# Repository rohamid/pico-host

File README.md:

# PICO HOST #
RP2040 board inspired by [Adafruit's RP2040 Feather Host](https://learn.adafruit.com/adafruit-feather-rp2040-with-usb-type-a-host). Board features:
* JST XH Li-ion/Li-po battery connector.
* Battery charger circuit.
* USB A Female connector for [PIO based USB](https://github.com/sekigon-gonnoc/Pico-PIO-USB).
* Adafruit's `STEMMA QT` I2C connector.

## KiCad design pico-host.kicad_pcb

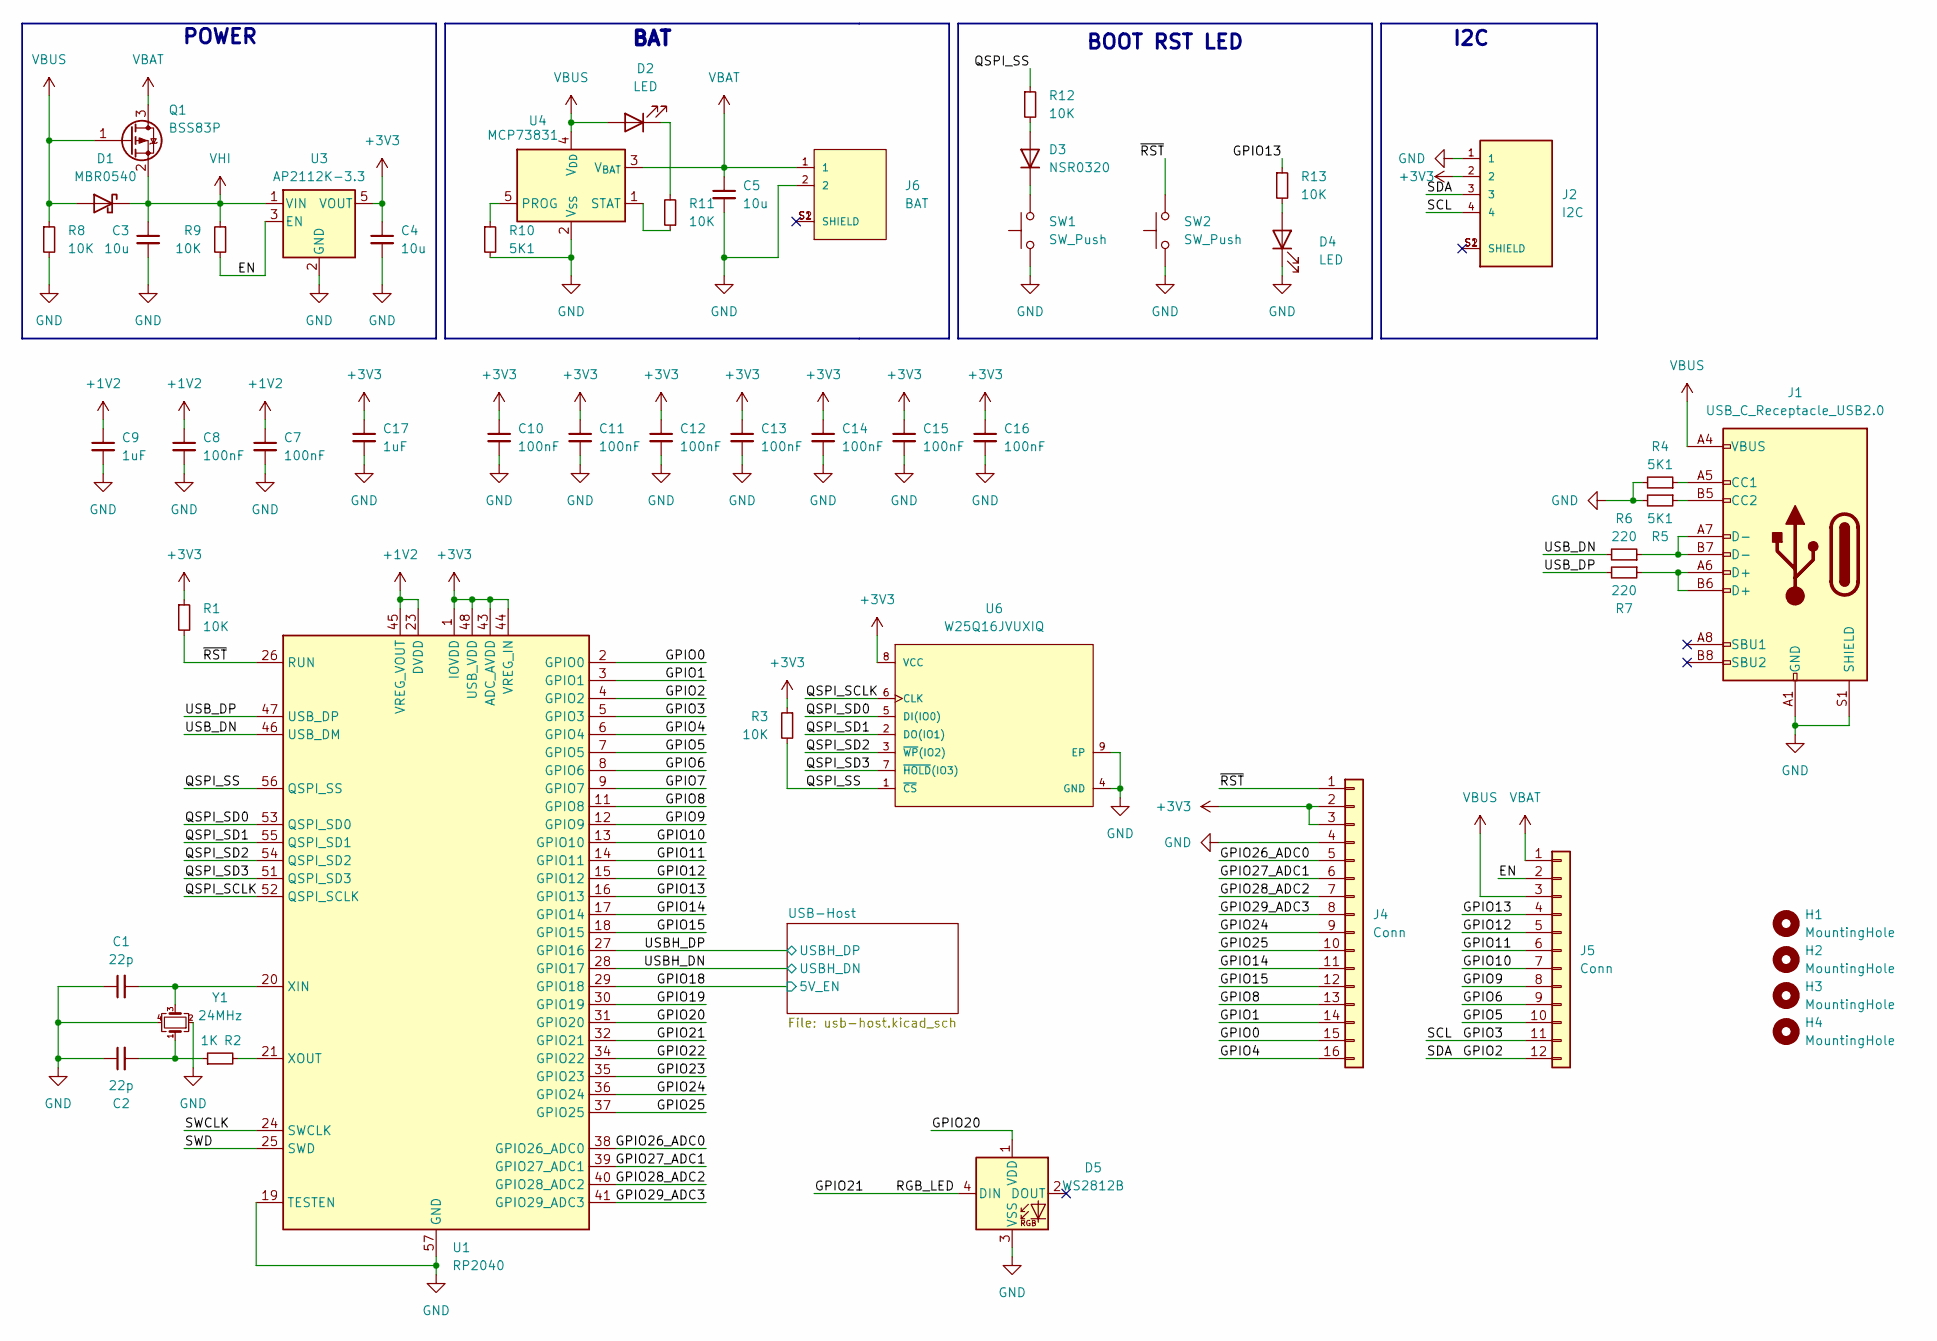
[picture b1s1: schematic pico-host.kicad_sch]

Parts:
C1, C2: 22p; C_0402_1005Metric
C3, C4, C5: 10u; C_0603_1608Metric
C7, C8, C10, C11, C12, C13, C14, C15, C16: 100nF; C_0402_1005Metric
C9: 1uF; C_0402_1005Metric
C17: 1uF; C_0603_1608Metric
D1: MBR0540; D_SOD-323
D2, D4: LED; LED_0603_1608Metric
D3: NSR0320; D_SOD-323
D5: WS2812B; LED_WS2812B-2020_PLCC4_2.0x2.0mm
H1, H2, H3, H4: MountingHole; MountingHole_2.5mm
J1: USB_C_Receptacle_USB2.0; USB_C_Receptacle_G-Switch_GT-USB-7010ASV
J2: I2C; JST_BM04B-SRSS-TB_LF__SN_
J4: Conn; PinHeader_1x16_P2.54mm_Vertical
J5: Conn; PinHeader_1x12_P2.54mm_Vertical
J6: BAT; JST_S2B-PH-SM4-TB_LF__SN_
Q1: BSS83P; TRANS_DMG3415UFY4Q-7
R1, R3, R8, R9, R11, R12, R13: 10K; R_0402_1005Metric
R2: 1K; R_0402_1005Metric
R4, R5, R10: 5K1; R_0402_1005Metric
R6, R7: 220; R_0402_1005Metric
SW1, SW2: SW_Push; SW_SPST_PTS810
U1: RP2040; QFN-56-1EP_7x7mm_P0.4mm_EP3.2x3.2mm
U3: AP2112K-3.3; SOT-23-5
U4: MCP73831; SOT-23-5
U6: W25Q16JVUXIQ; Winbond-UX-0-0-IPC_B; mouser part number 454-W25Q16JVUXIQTR; digikey description IC FLASH 16MBIT SPI/QUAD 8USON
Y1: 24MHz; Crystal_SMD_2520-4Pin_2.5x2.0mm

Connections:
+1V2: C7.1, C8.1, C9.1, U1.23 (DVDD), U1.45 (VREG_VOUT), U1.50 (DVDD)
+3V3: C4.1, C10.1, C11.1, C12.1, C13.1, C14.1, C15.1, C16.1, C17.1, J2.2, J4.2, J4.3, R1.1, R3.1, U1.1 (IOVDD), U1.10 (IOVDD), U1.22 (IOVDD), U1.33 (IOVDD), U1.42 (IOVDD), U1.43 (ADC_AVDD), U1.44 (VREG_IN), U1.48 (USB_VDD), U1.49 (IOVDD), U3.5 (VOUT), U6.8 (VCC); also elsewhere on the board
/EN: J5.2, R9.2, U3.3 (EN)
/GPIO0: J4.15, U1.2 (GPIO0)
/GPIO1: J4.14, U1.3 (GPIO1)
/GPIO2: J2.3, J5.12, U1.4 (GPIO2)
/GPIO3: J2.4, J5.11, U1.5 (GPIO3)
/GPIO4: J4.16, U1.6 (GPIO4)
/GPIO5: J5.10, U1.7 (GPIO5)
/GPIO6: J5.9, U1.8 (GPIO6)
/GPIO7: U1.9 (GPIO7)
/GPIO8: J4.13, U1.11 (GPIO8)
/GPIO9: J5.8, U1.12 (GPIO9)
/GPIO10: J5.7, U1.13 (GPIO10)
/GPIO11: J5.6, U1.14 (GPIO11)
/GPIO12: J5.5, U1.15 (GPIO12)
/GPIO13: J5.4, R13.1, U1.16 (GPIO13)
/GPIO14: J4.11, U1.17 (GPIO14)
/GPIO15: J4.12, U1.18 (GPIO15)
/GPIO18: U1.29 (GPIO18); also elsewhere on the board
/GPIO19: U1.30 (GPIO19)
/GPIO20: D5.1 (VDD), U1.31 (GPIO20)
/GPIO21: D5.4 (DIN), U1.32 (GPIO21)
/GPIO22: U1.34 (GPIO22)
/GPIO23: U1.35 (GPIO23)
/GPIO24: J4.9, U1.36 (GPIO24)
/GPIO25: J4.10, U1.37 (GPIO25)
/GPIO26_ADC0: J4.5, U1.38 (GPIO26_ADC0)
/GPIO27_ADC1: J4.6, U1.39 (GPIO27_ADC1)
/GPIO28_ADC2: J4.7, U1.40 (GPIO28_ADC2)
/GPIO29_ADC3: J4.8, U1.41 (GPIO29_ADC3)
/QSPI_SCLK: U1.52 (QSPI_SCLK), U6.6 (CLK)
/QSPI_SD0: U1.53 (QSPI_SD0), U6.5 (DI(IO0))
/QSPI_SD1: U1.55 (QSPI_SD1), U6.2 (DO(IO1))
/QSPI_SD2: U1.54 (QSPI_SD2), U6.3 (~WP(IO2))
/QSPI_SD3: U1.51 (QSPI_SD3), U6.7 (~HOLD(IO3))
/QSPI_SS: R3.2, R12.1, U1.56 (QSPI_SS), U6.1 (~CS)
/SWCLK: U1.24 (SWCLK)
/SWD: U1.25 (SWD)
/USBH_DN: U1.28 (GPIO17); also elsewhere on the board
/USBH_DP: U1.27 (GPIO16); also elsewhere on the board
/USB_DN: R6.2, U1.46 (USB_DM)
/USB_DP: R7.2, U1.47 (USB_DP)
/~RST: J4.1, R1.2, SW2.2, U1.26 (RUN)
GND: C1.1, C2.1, C3.2, C4.2, C5.2, C7.2, C8.2, C9.2, C10.2, C11.2, C12.2, C13.2, C14.2, C15.2, C16.2, C17.2, D4.1 (K), D5.3 (VSS), J1.A1 (GND), J1.A12 (GND), J1.B1 (GND), J1.B12 (GND), J1.S1 (SHIELD), J2.1, J4.4, J6.2, R4.2, R5.2, R8.2, R10.2, SW1.1, SW2.1, U1.19 (TESTEN), U1.57 (GND), U3.2 (GND), U4.2 (V_{SS}), U6.4 (GND), U6.9 (EP), Y1.2, Y1.4; also elsewhere on the board
unnamed: C2.2, R2.1, Y1.1
unnamed: D2.1 (K), R11.2
unnamed: D3.2 (A), R12.2
unnamed: D3.1 (K), SW1.2
unnamed: D4.2 (A), R13.2
unnamed: J1.A5 (CC1), R4.1
unnamed: J1.B5 (CC2), R5.1
unnamed: J1.A6 (D+), J1.B6 (D+), R7.1
unnamed: J1.A7 (D-), J1.B7 (D-), R6.1
unnamed: C1.2, U1.20 (XIN), Y1.3
unnamed: R2.2, U1.21 (XOUT)
unnamed: R10.1, U4.5 (PROG)
unnamed: R11.1, U4.1 (STAT)
VBAT: C5.1, J5.1, J6.1, Q1.3 (D), U4.3 (V_{BAT})
VBUS: D1.2 (A), D2.2 (A), J1.A4 (VBUS), J1.A9 (VBUS), J1.B4 (VBUS), J1.B9 (VBUS), J5.3, Q1.1 (G), R8.1, U4.4 (V_{DD})
VHI: C3.1, D1.1 (K), Q1.2 (S), R9.1, U3.1 (VIN); also elsewhere on the board

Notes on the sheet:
BAT
I2C
POWER
BOOT RST LED

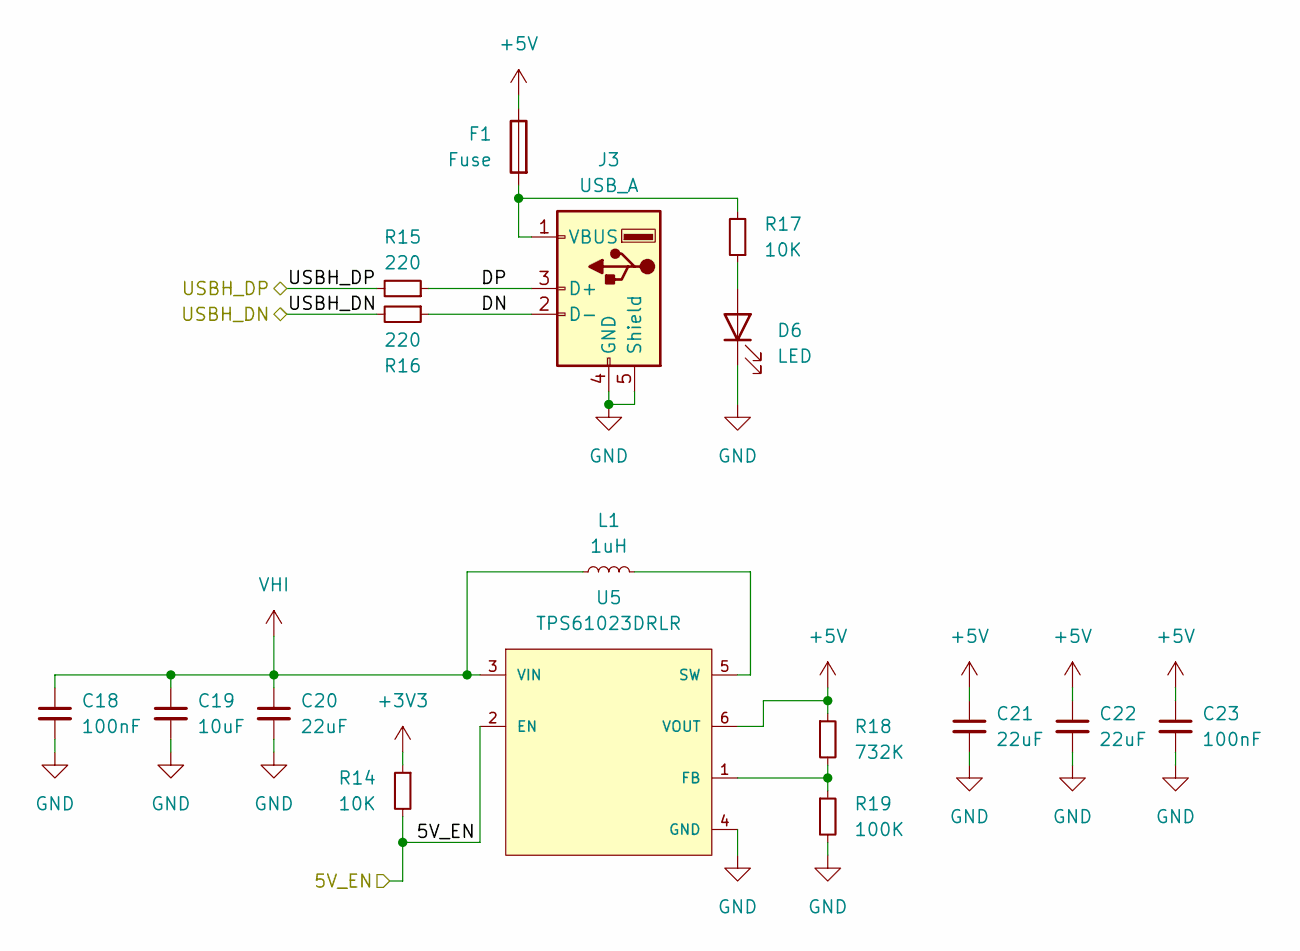
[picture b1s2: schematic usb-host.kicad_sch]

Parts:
C18, C23: 100nF; C_0402_1005Metric
C19: 10uF; C_0603_1608Metric
C20, C21, C22: 22uF; C_0603_1608Metric
D6: LED; LED_0603_1608Metric
F1: Fuse; Fuse_0805_2012Metric
J3: USB_A; USB_A_Molex_67643_Horizontal
L1: 1uH; L_1210_3225Metric
R14, R17: 10K; R_0402_1005Metric
R15, R16: 220; R_0402_1005Metric
R18: 732K; R_0402_1005Metric
R19: 100K; R_0402_1005Metric
U5: TPS61023DRLR; SOT-563; output voltage 2.2-5.5V; mouser part number 595-TPS61023DRLR; digikey description FINISH GOODS FOR TPS61023

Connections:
+3V3: R14.1; also elsewhere on the board
+5V: C21.1, C22.1, C23.1, F1.1, R18.1, U5.6 (VOUT)
/GPIO18: R14.2, U5.2 (EN); also elsewhere on the board
/USB-Host/DN: J3.2 (D-), R16.1
/USB-Host/DP: J3.3 (D+), R15.1
/USBH_DN: R16.2; also elsewhere on the board
/USBH_DP: R15.2; also elsewhere on the board
GND: C18.2, C19.2, C20.2, C21.2, C22.2, C23.2, D6.1 (K), J3.4 (GND), J3.5 (Shield), R19.2, U5.4 (GND); also elsewhere on the board
unnamed: D6.2 (A), R17.1
unnamed: F1.2, J3.1 (VBUS), R17.2
unnamed: R18.2, R19.1, U5.1 (FB)
unnamed: L1.2, U5.5 (SW)
VHI: C18.1, C19.1, C20.1, L1.1, U5.3 (VIN); also elsewhere on the board

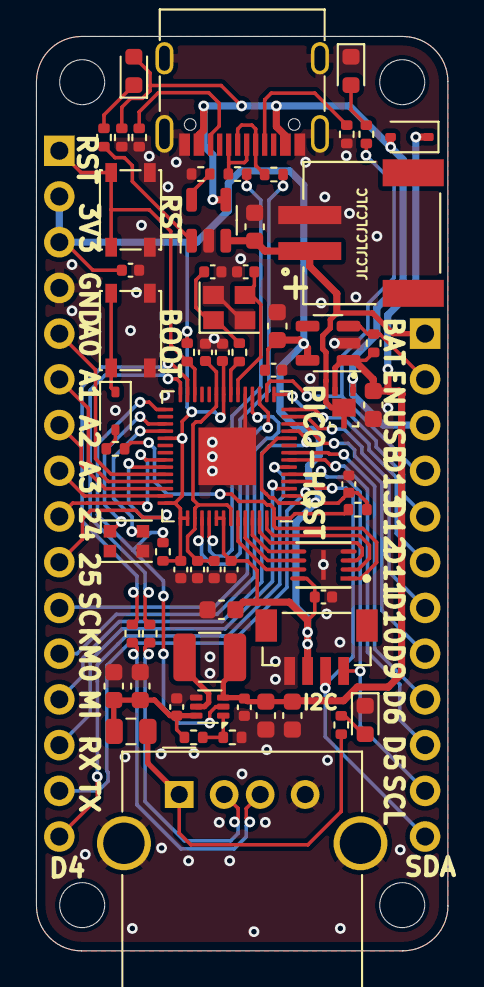
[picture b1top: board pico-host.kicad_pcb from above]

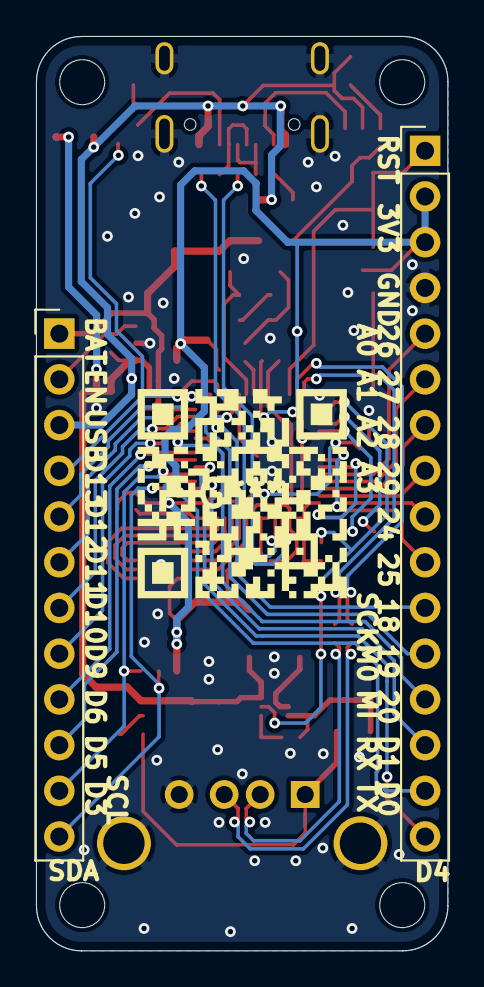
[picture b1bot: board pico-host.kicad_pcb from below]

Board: 2 copper layers, 22.9 x 50.8 mm, 68 parts (2 on the bottom side), 62 nets.

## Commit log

2024-03-18 Tracks almost finished
2024-03-19 Finished Tracks
2024-03-19 Updated .gitignore
2024-04-28 Added qr logo, doc/images, updated README
